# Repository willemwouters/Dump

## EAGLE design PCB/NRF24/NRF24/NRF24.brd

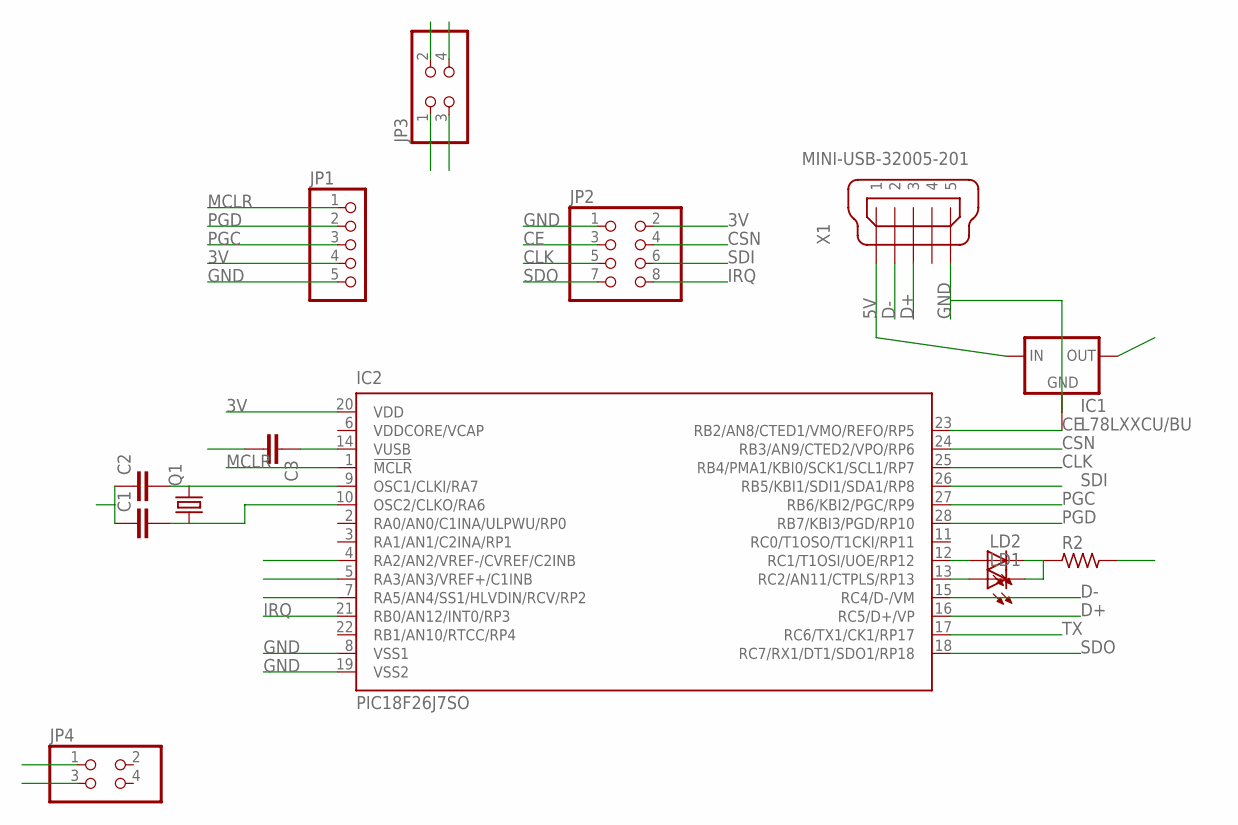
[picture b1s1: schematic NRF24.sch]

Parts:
C1, C2: C-EU025-025X050; C025-025X050
C3: C-EU050-025X075; C050-025X075
IC1: L78LXXCU/BU; SOT89
IC2: PIC18F26J7SO; SO28W
JP1: PINHD-1X5; 1X05
JP2: PINHD-2X4; 2X04
JP3, JP4: PINHD-2X2; 2X02
LD1, LD2: LED5MM
Q1: CRYTALHC49S; HC49/S
R2: R_X0204/5; 0204/5
X1: MINI-USB-32005-201; 32005-201

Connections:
3V: IC1.1 (OUT), IC2.20 (VDD), JP1.4, JP2.2
5V: IC1.3 (IN), X1.1
CE: IC2.23 (RB2/AN8/CTED1/VMO/REFO/RP5), JP2.3
CLK: IC2.25 (RB4/PMA1/KBI0/SCK1/SCL1/RP7), JP2.5
CSN: IC2.24 (RB3/AN9/CTED2/VPO/RP6), JP2.4
D+: IC2.16 (RC5/D+/VP), X1.3
D-: IC2.15 (RC4/D-/VM), X1.2
GND: C1.1, C2.1, C3.2, IC1.2 (GND), IC2.8 (VSS1), IC2.19 (VSS2), JP1.5, JP2.1, R2.2, X1.5
IRQ: IC2.21 (RB0/AN12/INT0/RP3), JP2.8
MCLR: IC2.1 (!MCLR), JP1.1
unnamed: IC2.13 (RC2/AN11/CTPLS/RP13), LD1.A
unnamed: LD1.K (C), LD2.K (C), R2.1
unnamed: IC2.12 (RC1/T1OSI/UOE/RP12), LD2.A
unnamed: C1.2, IC2.10 (OSC2/CLKO/RA6), Q1.1
unnamed: C2.2, IC2.9 (OSC1/CLKI/RA7), Q1.2
unnamed: C3.1, IC2.14 (VUSB)
PGC: IC2.27 (RB6/KBI2/PGC/RP9), JP1.3
PGD: IC2.28 (RB7/KBI3/PGD/RP10), JP1.2
RA2: IC2.4 (RA2/AN2/VREF-/CVREF/C2INB), JP3.1
RA3: IC2.5 (RA3/AN3/VREF+/C1INB), JP3.3
RA5: IC2.7 (RA5/AN4/SS1/HLVDIN/RCV/RP2), JP3.2
SDI: IC2.26 (RB5/KBI1/SDI1/SDA1/RP8), JP2.6
SDO: IC2.18 (RC7/RX1/DT1/SDO1/RP18), JP2.7, JP4.1
TX: IC2.17 (RC6/TX1/CK1/RP17), JP4.3

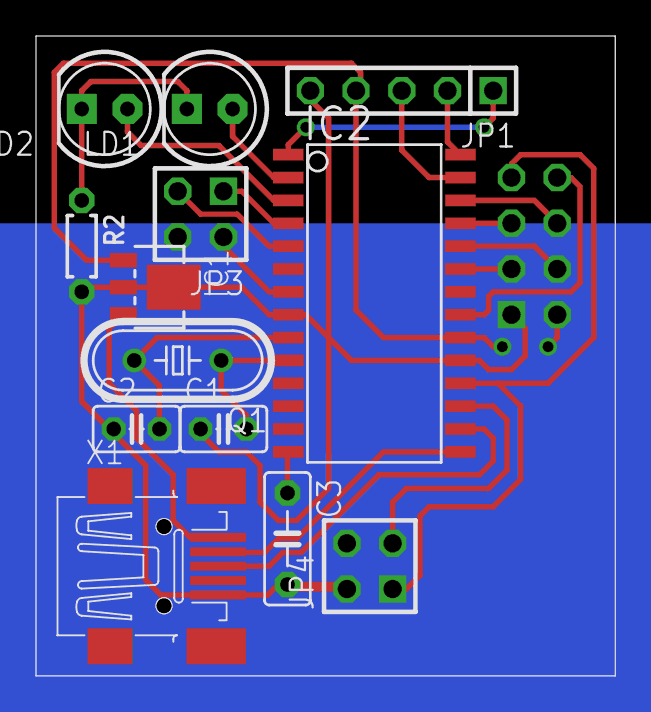
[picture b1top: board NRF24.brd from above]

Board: 2 copper layers, 32.2 x 35.5 mm, 14 parts (1 on the bottom side), 24 nets.

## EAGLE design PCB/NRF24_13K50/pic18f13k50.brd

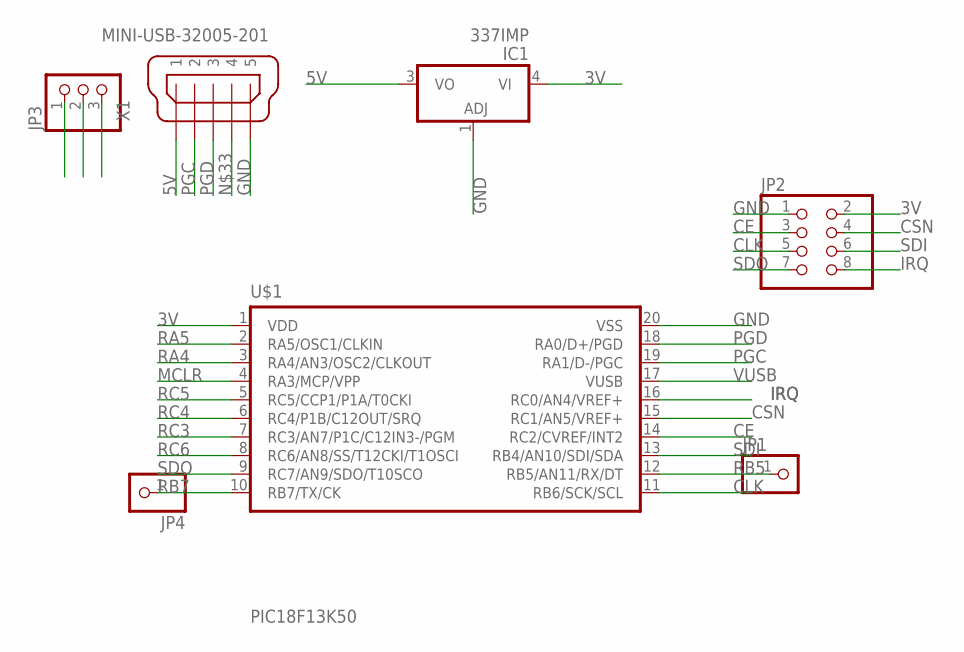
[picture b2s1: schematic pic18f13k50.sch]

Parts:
IC1: 337IMP; SOT223
JP1, JP4: PINHD-1X1; 1X01
JP2: PINHD-2X4; 2X04
JP3: PINHD-1X3; 1X03
U$1: PIC18F13K50; SSOP20
X1: MINI-USB-32005-201; 32005-201

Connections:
3V: IC1.4 (VI), JP2.2, JP3.2, U$1.1 (VDD)
5V: IC1.3 (VO), JP3.3, X1.1
CE: JP2.3, U$1.14 (RC2/CVREF/INT2)
CLK: JP2.5, U$1.11 (RB6/SCK/SCL)
CSN: JP2.4, U$1.15 (RC1/AN5/VREF+)
GND: IC1.1 (ADJ), JP2.1, U$1.20 (VSS), X1.5
IRQ: JP2.8, U$1.16 (RC0/AN4/VREF+)
MCLR: JP3.1, U$1.4 (RA3/MCP/VPP)
PGC: U$1.19 (RA1/D-/PGC), X1.2
PGD: U$1.18 (RA0/D+/PGD), X1.3
RA4: U$1.3 (RA4/AN3/OSC2/CLKOUT)
RA5: U$1.2 (RA5/OSC1/CLKIN)
RB5: JP1.1, U$1.12 (RB5/AN11/RX/DT)
RB7: JP4.1, U$1.10 (RB7/TX/CK)
RC3: U$1.7 (RC3/AN7/P1C/C12IN3-/PGM)
RC4: U$1.6 (RC4/P1B/C12OUT/SRQ)
RC5: U$1.5 (RC5/CCP1/P1A/T0CKI)
RC6: U$1.8 (RC6/AN8/SS/T12CKI/T1OSCI)
SDI: JP2.6, U$1.13 (RB4/AN10/SDI/SDA)
SDO: JP2.7, U$1.9 (RC7/AN9/SDO/T10SCO)
VUSB: U$1.17 (VUSB)

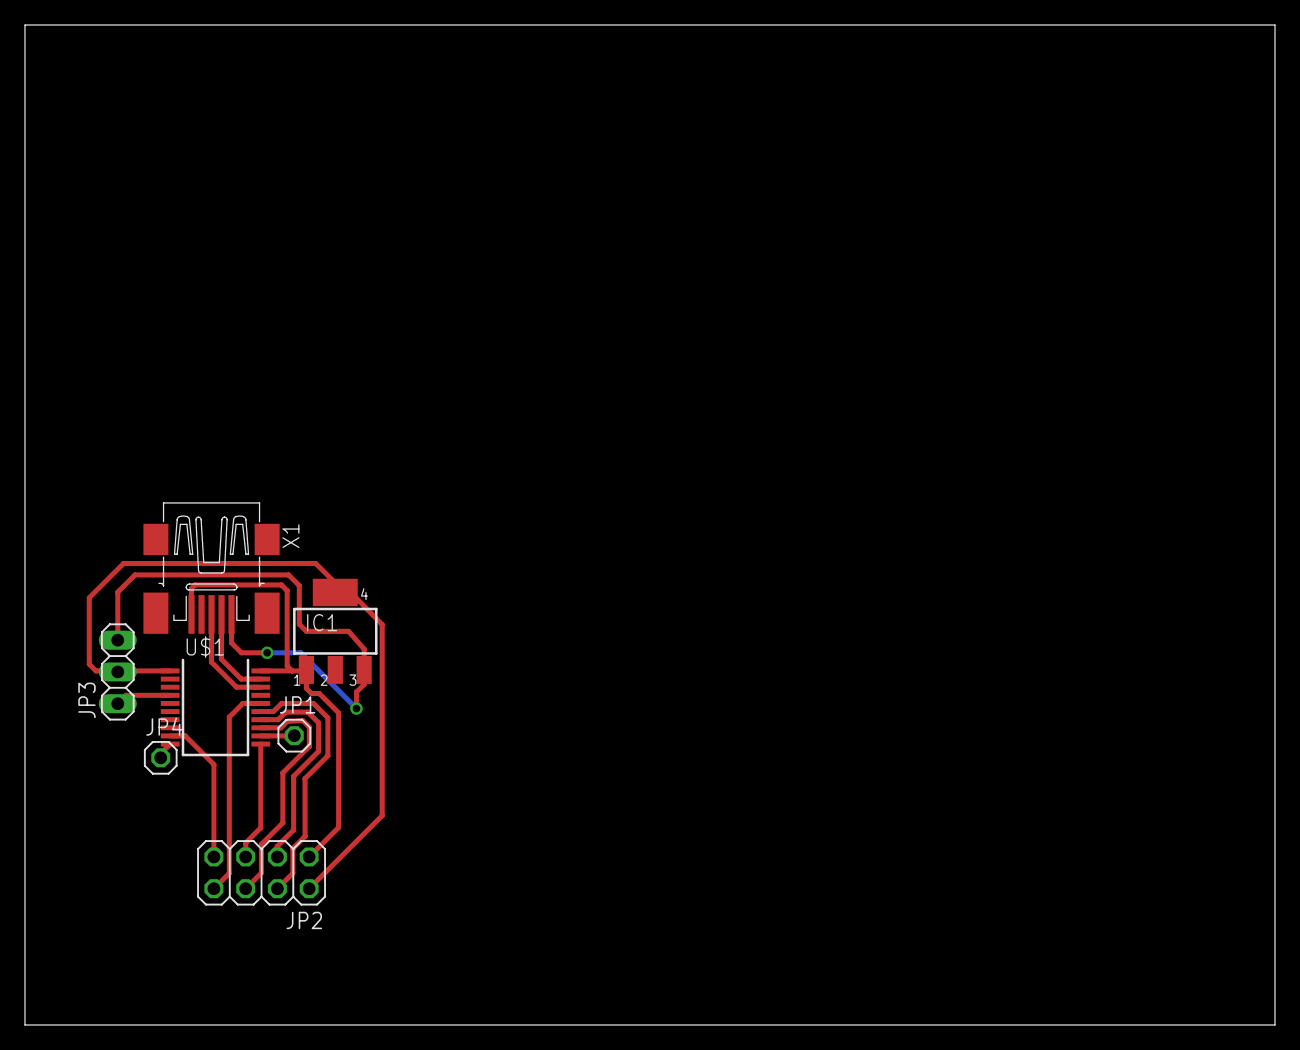
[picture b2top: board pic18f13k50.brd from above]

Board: 2 copper layers, 100.0 x 80.0 mm, 7 parts (0 on the bottom side), 14 nets.

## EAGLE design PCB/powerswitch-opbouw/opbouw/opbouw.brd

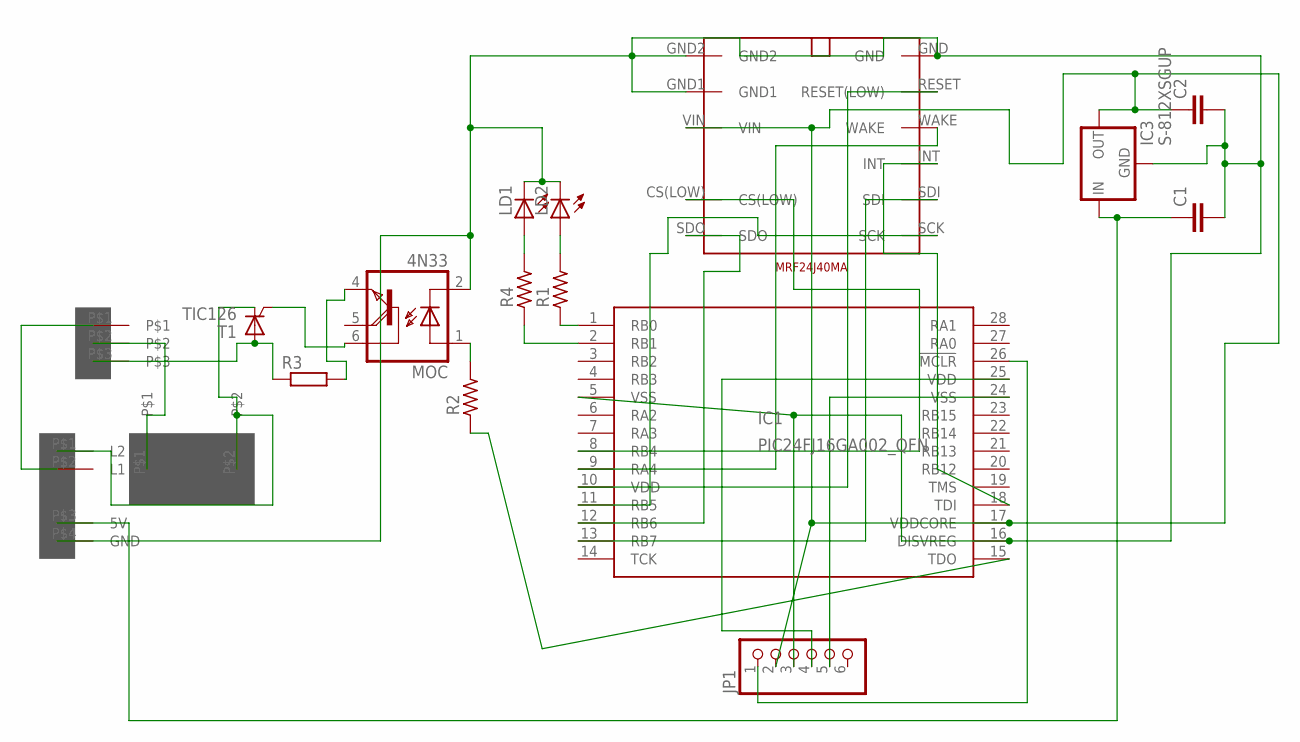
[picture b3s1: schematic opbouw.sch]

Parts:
C1, C2: C-EUC0805K; C0805K
IC1: PIC24FJ16GA002_QFN; QFN28-ML_6X6MM
IC3: S-812XSGUP; SOT89
JP1: PINHD-1X6; 1X06
LD1, LD2: LEDCHIPLED_0805; CHIPLED_0805
MOC: 4N33; DIL06
R1, R2, R4: R_0805; R0805
R3: R-EU_0207/10; 0207/10
T1: TIC126; TO220CS
U$1: MRF24J40MA
U$2: CONNECTOR
U$3: FUSEFUSE; FUSE
U$4: BIAS

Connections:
unnamed: C2.1, IC1.17 (VDDCORE), IC3.3 (OUT), JP1.2, U$1.VIN
unnamed: IC1.26 (!MCLR), JP1.1
unnamed: IC1.25 (VDD), JP1.4
unnamed: IC1.24 (VSS), JP1.5
unnamed: IC1.8 (RB4), U$1.CS(LOW)
unnamed: IC1.15 (TDO), R2.1
unnamed: IC1.10 (VDD), U$1.RESET (RESET(LOW))
unnamed: IC1.13 (RB7), U$1.SDI
unnamed: IC1.18 (TDI), U$1.INT
unnamed: IC1.9 (RA4), U$1.WAKE
unnamed: IC1.11 (RB5), U$1.SCK
unnamed: MOC.6 (B), T1.G
unnamed: MOC.1 (A), R2.2
unnamed: IC1.12 (RB6), U$1.SDO
unnamed: MOC.4 (E), R3.2
unnamed: U$2.P$2, U$3.P$1
unnamed: R3.1, T1.A, U$2.P$3
unnamed: IC1.1 (RB0), R1.1
unnamed: IC1.2 (RB1), R4.1
unnamed: LD2.A, R1.2
unnamed: LD1.A, R4.2
unnamed: C1.2, C2.2, IC1.5 (VSS), IC1.16 (DISVREG), IC3.1 (GND), JP1.3, LD1.C, LD2.C, MOC.2 (C), U$1.GND, U$1.GND1, U$1.GND2, U$4.P$4 (GND)
unnamed: C1.1, IC3.2 (IN), U$4.P$3 (5V)
unnamed: T1.C, U$3.P$2, U$4.P$1 (L2)
unnamed: U$2.P$1, U$4.P$2 (L1)

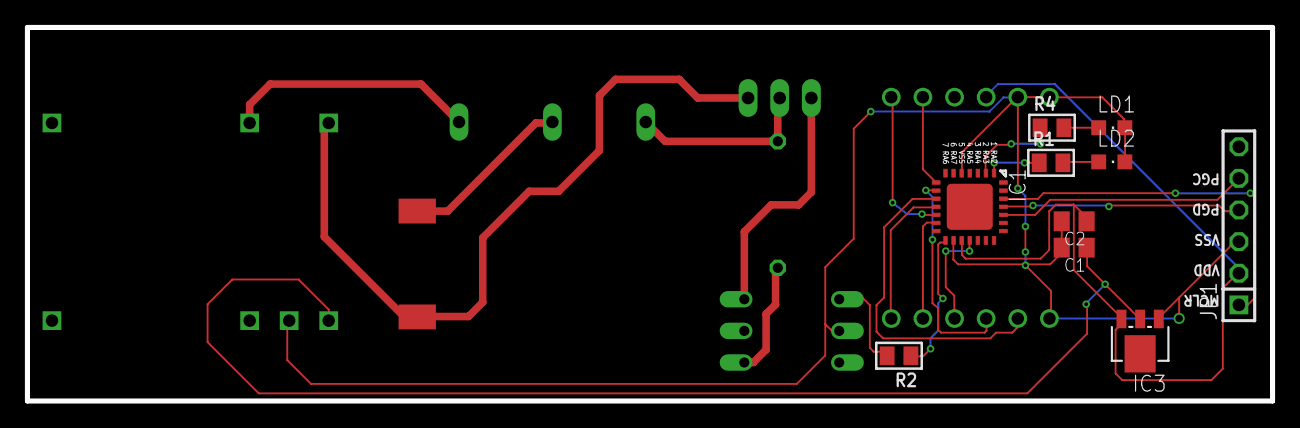
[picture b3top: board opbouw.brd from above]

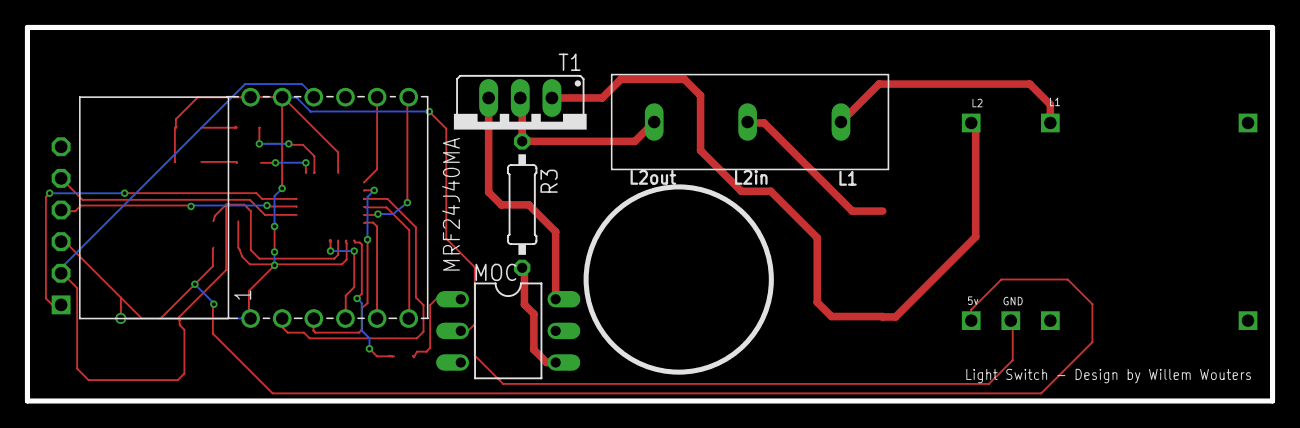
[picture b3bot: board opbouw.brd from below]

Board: 2 copper layers, 100.0 x 30.0 mm, 17 parts (5 on the bottom side), 25 nets.

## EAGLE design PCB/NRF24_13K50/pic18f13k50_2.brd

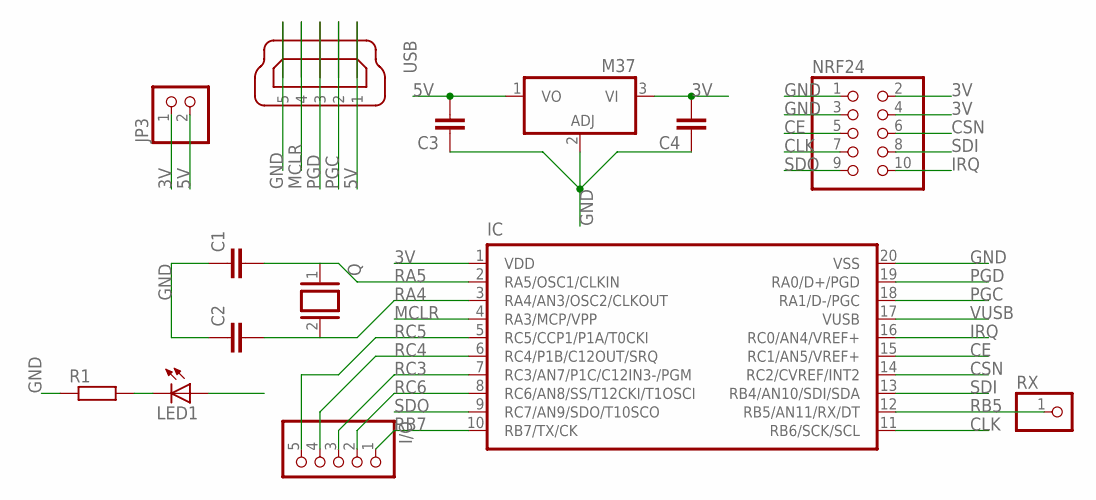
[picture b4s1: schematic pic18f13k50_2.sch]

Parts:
C1, C2: C-EUC0805; C0805
C3, C4: C-EU025-025X050; C025-025X050
I/O: PINHD-1X5; 1X05
IC: PIC18F13K50; SSOP20
JP3: PINHD-1X2; 1X02
LED1: LEDCHIP-LED0805; CHIP-LED0805
M37: 337IMP; SOT223
NRF24: PINHD-2X5; 2X05
Q: XTAL/S; QS
R1: R; R0805
RX: PINHD-1X1; 1X01
USB: MINI-USB-32005-201; 32005-201

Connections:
3V: C4.2, IC.1 (VDD), JP3.1, M37.3 (VI), NRF24.2, NRF24.4
5V: C3.2, JP3.2, M37.1 (VO), USB.1
CE: IC.15 (RC1/AN5/VREF+), NRF24.5
CLK: IC.11 (RB6/SCK/SCL), NRF24.7
CSN: IC.14 (RC2/CVREF/INT2), NRF24.6
GND: C1.1, C2.1, C3.1, C4.1, IC.20 (VSS), M37.2 (ADJ), NRF24.1, NRF24.3, R1.1, USB.5
IRQ: IC.16 (RC0/AN4/VREF+), NRF24.10
MCLR: IC.4 (RA3/MCP/VPP), USB.4
unnamed: LED1.C, R1.2
PGC: IC.18 (RA1/D-/PGC), USB.2
PGD: IC.19 (RA0/D+/PGD), USB.3
RA4: C2.2, IC.3 (RA4/AN3/OSC2/CLKOUT), Q.2
RA5: C1.2, IC.2 (RA5/OSC1/CLKIN), Q.1
RB5: IC.12 (RB5/AN11/RX/DT), RX.1
RB7: I/O.1, IC.10 (RB7/TX/CK), LED1.A
RC3: I/O.3, IC.7 (RC3/AN7/P1C/C12IN3-/PGM)
RC4: I/O.4, IC.6 (RC4/P1B/C12OUT/SRQ)
RC5: I/O.5, IC.5 (RC5/CCP1/P1A/T0CKI)
RC6: I/O.2, IC.8 (RC6/AN8/SS/T12CKI/T1OSCI)
SDI: IC.13 (RB4/AN10/SDI/SDA), NRF24.8
SDO: IC.9 (RC7/AN9/SDO/T10SCO), NRF24.9
VUSB: IC.17 (VUSB)

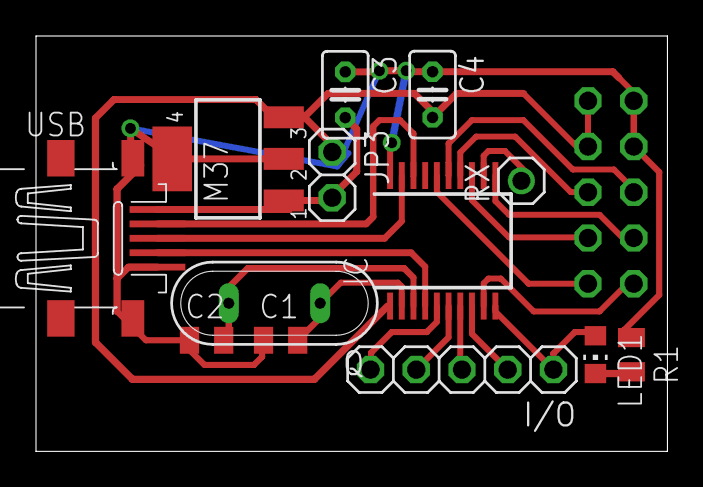
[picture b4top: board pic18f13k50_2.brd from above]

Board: 2 copper layers, 35.1 x 23.1 mm, 14 parts (1 on the bottom side), 21 nets.

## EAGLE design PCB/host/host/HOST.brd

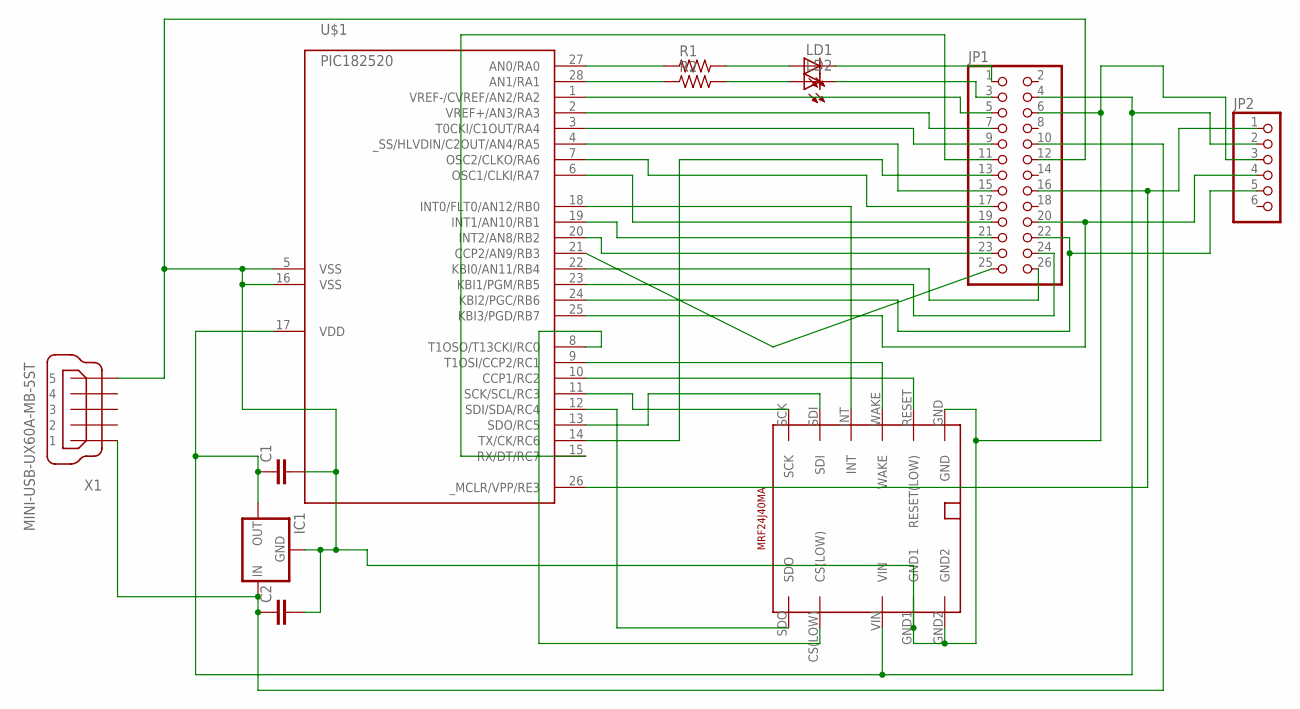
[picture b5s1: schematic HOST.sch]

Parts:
C1, C2: C-EUC0805; C0805
IC1: 78LXX-SOT89; SOT89
JP1: PINHD-2X13_2.54; 2X13
JP2: PINHD-1X6; 1X06
LD1, LD2: LEDCHIPLED_0805; CHIPLED_0805
R1, R2: R_0805; R0805
U$1: PIC182520; QFN28
U$2: MRF24J40MA
X1: MINI-USB-UX60A-MB-5ST; UX60A-MB-5ST

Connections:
unnamed: U$1.12 (SDI/SDA/RC4), U$2.SDO
unnamed: U$1.8 (T1OSO/T13CKI/RC0), U$2.CS(LOW)
unnamed: U$1.10 (CCP1/RC2), U$2.RESET (RESET(LOW))
unnamed: U$1.11 (SCK/SCL/RC3), U$2.SCK
unnamed: U$1.13 (SDO/RC5), U$2.SDI
unnamed: U$1.18 (INT0/FLT0/AN12/RB0), U$2.INT
unnamed: U$1.9 (T1OSI/CCP2/RC1), U$2.WAKE
unnamed: JP1.13, U$1.14 (TX/CK/RC6)
unnamed: C1.2, C2.2, IC1.1 (GND), JP1.6, JP1.12, JP2.3, U$1.5 (VSS), U$1.16 (VSS), U$2.GND, U$2.GND1, U$2.GND2, X1.5
unnamed: JP1.11, U$1.15 (RX/DT/RC7)
unnamed: C2.1, IC1.2 (IN), JP1.10, X1.1
unnamed: R1.1, U$1.27 (AN0/RA0)
unnamed: R2.1, U$1.28 (AN1/RA1)
unnamed: LD2.A, R2.2
unnamed: LD1.A, R1.2
unnamed: JP1.1, LD1.C
unnamed: JP1.3, LD2.C
unnamed: JP1.5, U$1.1 (VREF-/CVREF/AN2/RA2)
unnamed: JP1.7, U$1.2 (VREF+/AN3/RA3)
unnamed: JP1.9, U$1.3 (T0CKI/C1OUT/RA4)
unnamed: JP1.21, U$1.19 (INT1/AN10/RB1)
unnamed: JP1.19, U$1.6 (OSC1/CLKI/RA7)
unnamed: JP1.15, U$1.4 (_SS/HLVDIN/C2OUT/AN4/RA5)
unnamed: JP1.17, U$1.7 (OSC2/CLKO/RA6)
unnamed: JP1.23, U$1.20 (INT2/AN8/RB2)
unnamed: JP1.25, U$1.21 (CCP2/AN9/RB3)
unnamed: JP1.26, U$1.22 (KBI0/AN11/RB4)
unnamed: JP1.24, U$1.23 (KBI1/PGM/RB5)
unnamed: JP1.22, JP2.5, U$1.24 (KBI2/PGC/RB6)
unnamed: JP1.20, JP2.4, U$1.25 (KBI3/PGD/RB7)
unnamed: JP1.16, JP2.1, U$1.26 (_MCLR/VPP/RE3)
unnamed: C1.1, IC1.3 (OUT), JP1.4, JP2.2, U$1.17 (VDD), U$2.VIN

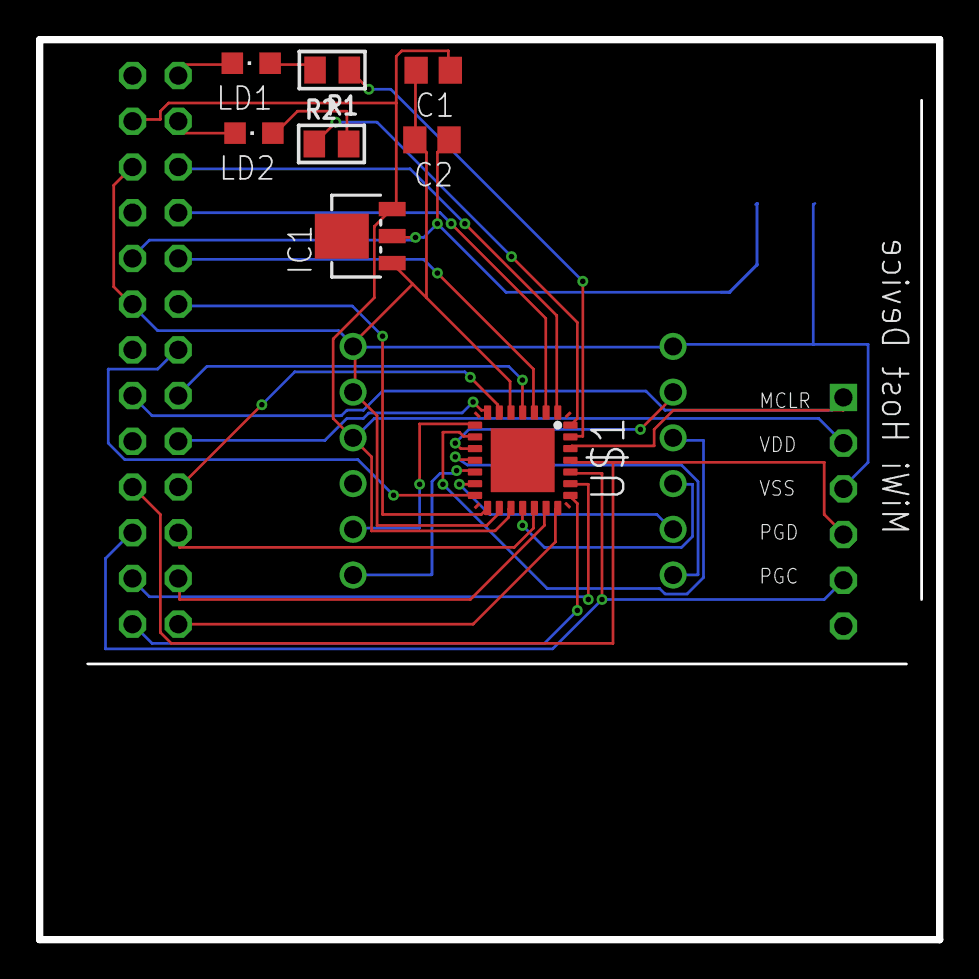
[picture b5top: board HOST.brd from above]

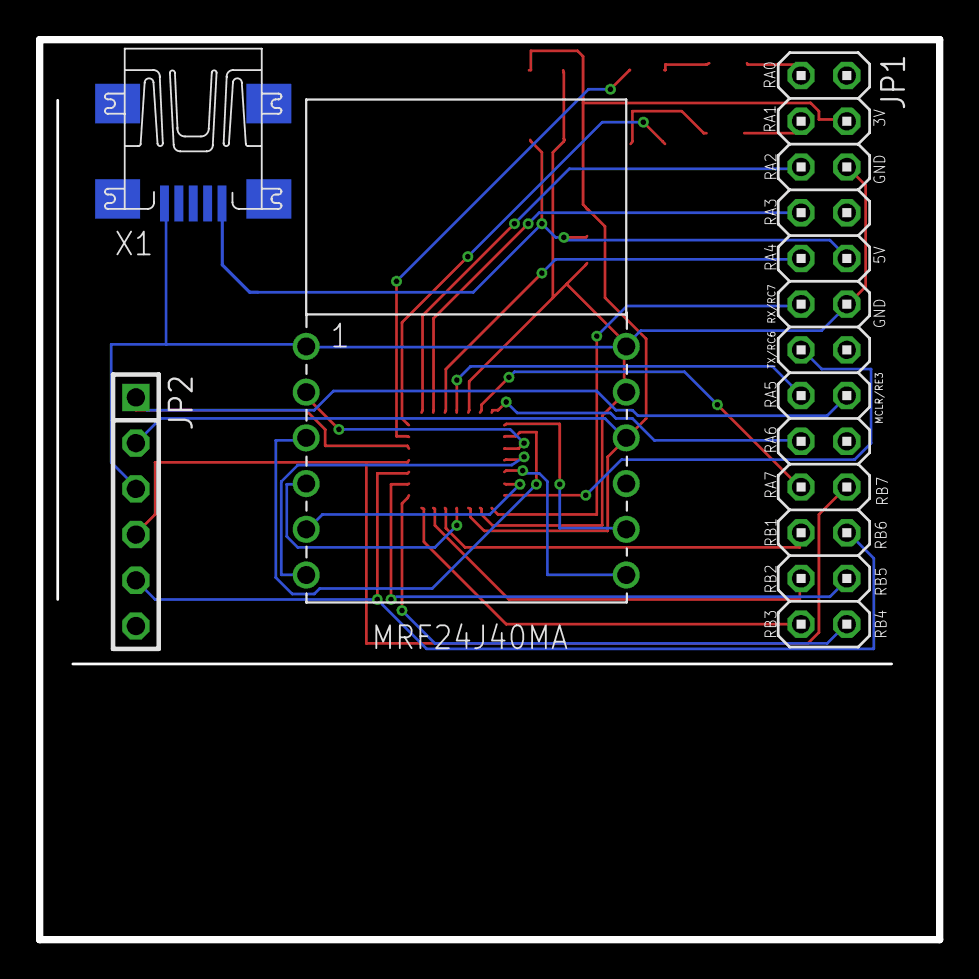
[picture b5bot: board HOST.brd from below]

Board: 2 copper layers, 50.0 x 50.0 mm, 12 parts (4 on the bottom side), 32 nets.

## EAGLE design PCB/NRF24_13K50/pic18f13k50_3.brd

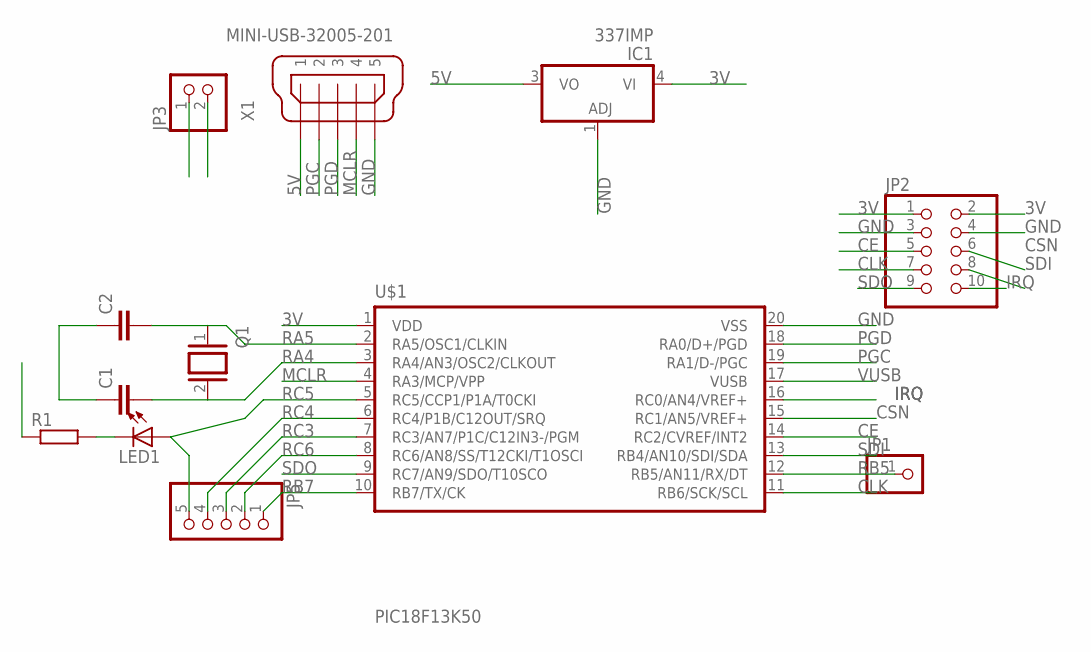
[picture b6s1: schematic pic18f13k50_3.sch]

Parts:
C1, C2: C-EUC0805; C0805
IC1: 337IMP; SOT223
JP1: PINHD-1X1; 1X01
JP2: PINHD-2X5; 2X05
JP3: PINHD-1X2; 1X02
JP5: PINHD-1X5; 1X05
LED1: LEDCHIP-LED0805; CHIP-LED0805
Q1: XTAL/S; QS
R1: R; R0805
U$1: PIC18F13K50; SSOP20
X1: MINI-USB-32005-201; 32005-201

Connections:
3V: IC1.4 (VI), JP2.1, JP2.2, JP3.1, R1.1, U$1.1 (VDD)
5V: IC1.3 (VO), JP3.2, X1.1
CE: JP2.5, U$1.14 (RC2/CVREF/INT2)
CLK: JP2.7, U$1.11 (RB6/SCK/SCL)
CSN: JP2.6, U$1.15 (RC1/AN5/VREF+)
GND: C1.1, C2.1, IC1.1 (ADJ), JP2.3, JP2.4, U$1.20 (VSS), X1.5
IRQ: JP2.10, U$1.16 (RC0/AN4/VREF+)
MCLR: U$1.4 (RA3/MCP/VPP), X1.4
unnamed: LED1.C, R1.2
PGC: U$1.19 (RA1/D-/PGC), X1.2
PGD: U$1.18 (RA0/D+/PGD), X1.3
RA4: C1.2, Q1.2, U$1.3 (RA4/AN3/OSC2/CLKOUT)
RA5: C2.2, Q1.1, U$1.2 (RA5/OSC1/CLKIN)
RB5: JP1.1, U$1.12 (RB5/AN11/RX/DT)
RB7: JP5.1, U$1.10 (RB7/TX/CK)
RC3: JP5.3, U$1.7 (RC3/AN7/P1C/C12IN3-/PGM)
RC4: JP5.4, U$1.6 (RC4/P1B/C12OUT/SRQ)
RC5: JP5.5, LED1.A, U$1.5 (RC5/CCP1/P1A/T0CKI)
RC6: JP5.2, U$1.8 (RC6/AN8/SS/T12CKI/T1OSCI)
SDI: JP2.8, U$1.13 (RB4/AN10/SDI/SDA)
SDO: JP2.9, U$1.9 (RC7/AN9/SDO/T10SCO)
VUSB: U$1.17 (VUSB)

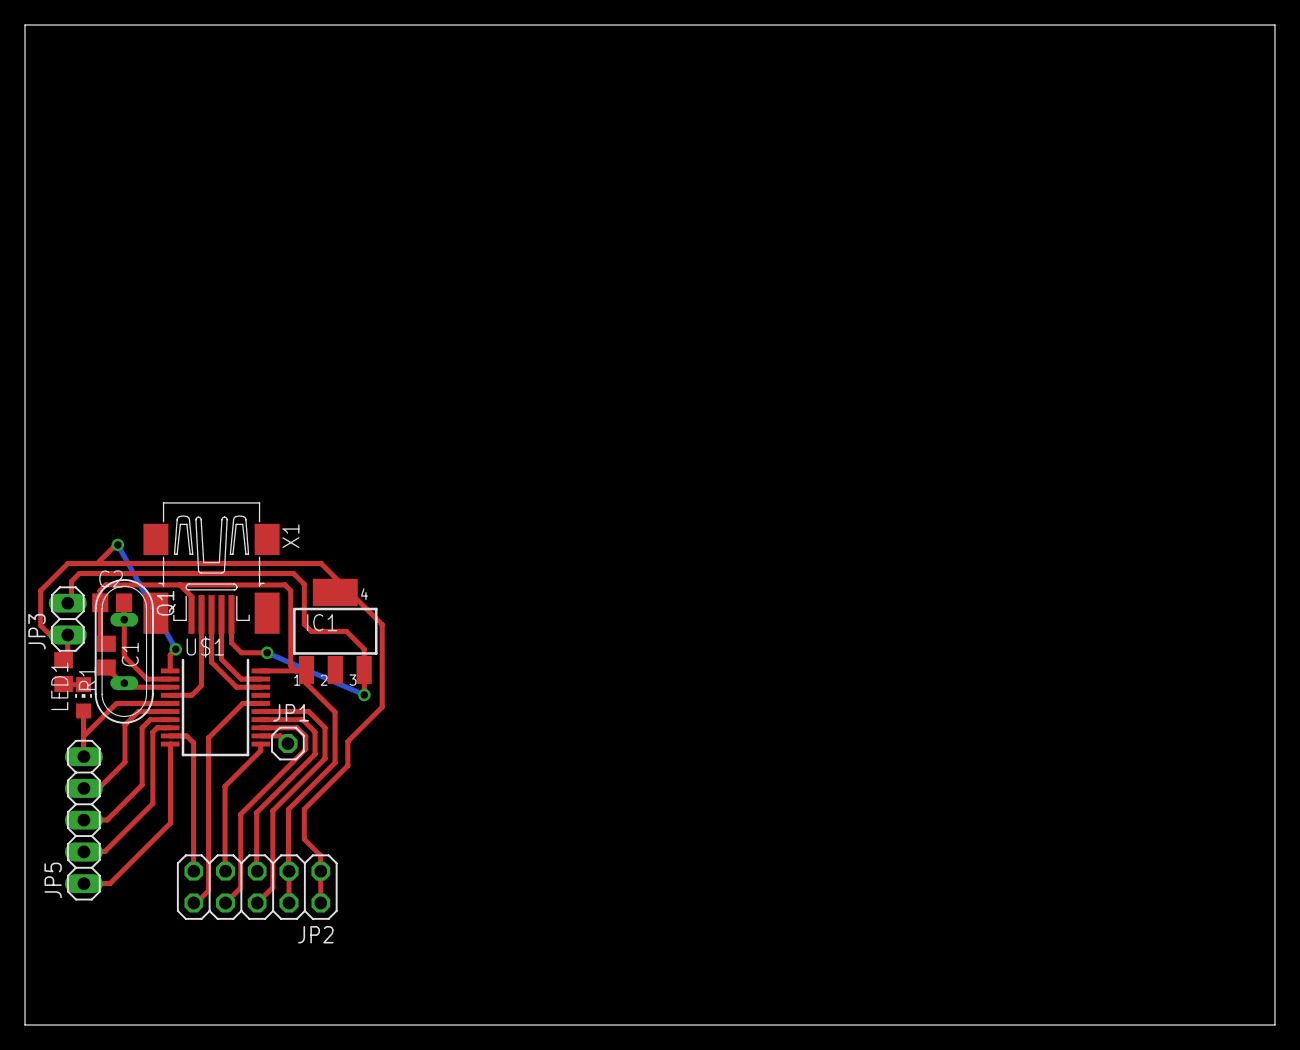
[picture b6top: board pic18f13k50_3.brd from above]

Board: 2 copper layers, 100.0 x 80.0 mm, 12 parts (0 on the bottom side), 21 nets.

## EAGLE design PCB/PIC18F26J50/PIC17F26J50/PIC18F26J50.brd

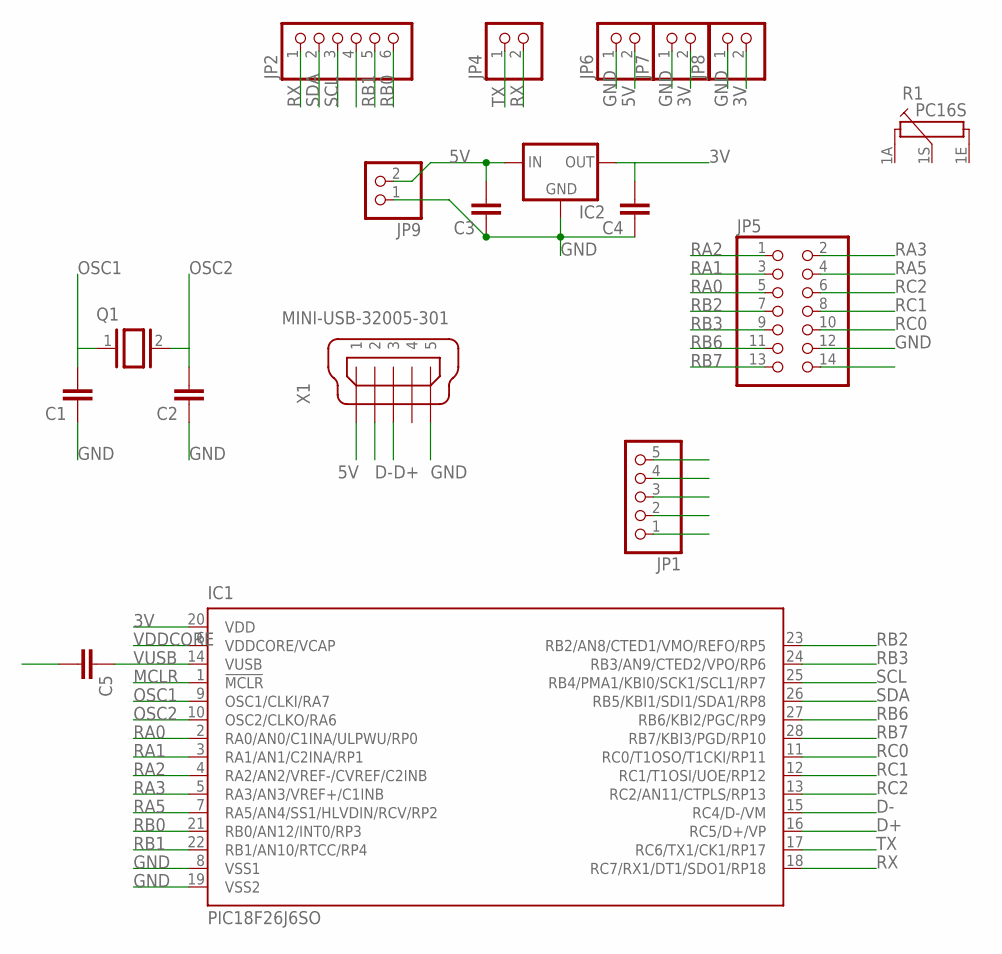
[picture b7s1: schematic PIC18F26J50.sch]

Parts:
C1, C2, C3, C4, C5: C-EU025-025X050; C025-025X050
IC1: PIC18F26J6SO; SO28W
IC2: 78LXX-SOT89; SOT89
JP1: PINHD-1X5; 1X05
JP2: PINHD-1X6; 1X06
JP4, JP6, JP7, JP8, JP9: PINHD-1X2; 1X02
JP5: PINHD-2X7; 2X07
Q1: XTAL/S; QS
R1: PC16S
X1: MINI-USB-32005-301; 32005-301

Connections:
3V: C4.2, IC1.20 (VDD), IC2.1 (OUT), JP1.4, JP7.2, JP8.2
5V: C3.2, IC2.3 (IN), JP6.2, JP9.2, X1.1
D+: IC1.16 (RC5/D+/VP), X1.3
D-: IC1.15 (RC4/D-/VM), X1.2
GND: C1.1, C2.1, C3.1, C4.1, C5.2, IC1.8 (VSS1), IC1.19 (VSS2), IC2.2 (GND), JP1.5, JP5.12, JP5.14, JP6.1, JP7.1, JP8.1, JP9.1, X1.5
MCLR: IC1.1 (!MCLR), JP1.1
OSC1: C1.2, IC1.9 (OSC1/CLKI/RA7), Q1.1
OSC2: C2.2, IC1.10 (OSC2/CLKO/RA6), Q1.2
RA0: IC1.2 (RA0/AN0/C1INA/ULPWU/RP0), JP5.5
RA1: IC1.3 (RA1/AN1/C2INA/RP1), JP5.3
RA2: IC1.4 (RA2/AN2/VREF-/CVREF/C2INB), JP5.1
RA3: IC1.5 (RA3/AN3/VREF+/C1INB), JP5.2
RA5: IC1.7 (RA5/AN4/SS1/HLVDIN/RCV/RP2), JP5.4
RB0: IC1.21 (RB0/AN12/INT0/RP3), JP2.6
RB1: IC1.22 (RB1/AN10/RTCC/RP4), JP2.5
RB2: IC1.23 (RB2/AN8/CTED1/VMO/REFO/RP5), JP2.4, JP5.7
RB3: IC1.24 (RB3/AN9/CTED2/VPO/RP6), JP5.9
RB6: IC1.27 (RB6/KBI2/PGC/RP9), JP1.2, JP5.11
RB7: IC1.28 (RB7/KBI3/PGD/RP10), JP1.3, JP5.13
RC0: IC1.11 (RC0/T1OSO/T1CKI/RP11), JP5.10
RC1: IC1.12 (RC1/T1OSI/UOE/RP12), JP5.8
RC2: IC1.13 (RC2/AN11/CTPLS/RP13), JP5.6
RX: IC1.18 (RC7/RX1/DT1/SDO1/RP18), JP2.1, JP4.2
SCL: IC1.25 (RB4/PMA1/KBI0/SCK1/SCL1/RP7), JP2.3
SDA: IC1.26 (RB5/KBI1/SDI1/SDA1/RP8), JP2.2
TX: IC1.17 (RC6/TX1/CK1/RP17), JP4.1
VDDCORE: IC1.6 (VDDCORE/VCAP)
VUSB: C5.1, IC1.14 (VUSB)

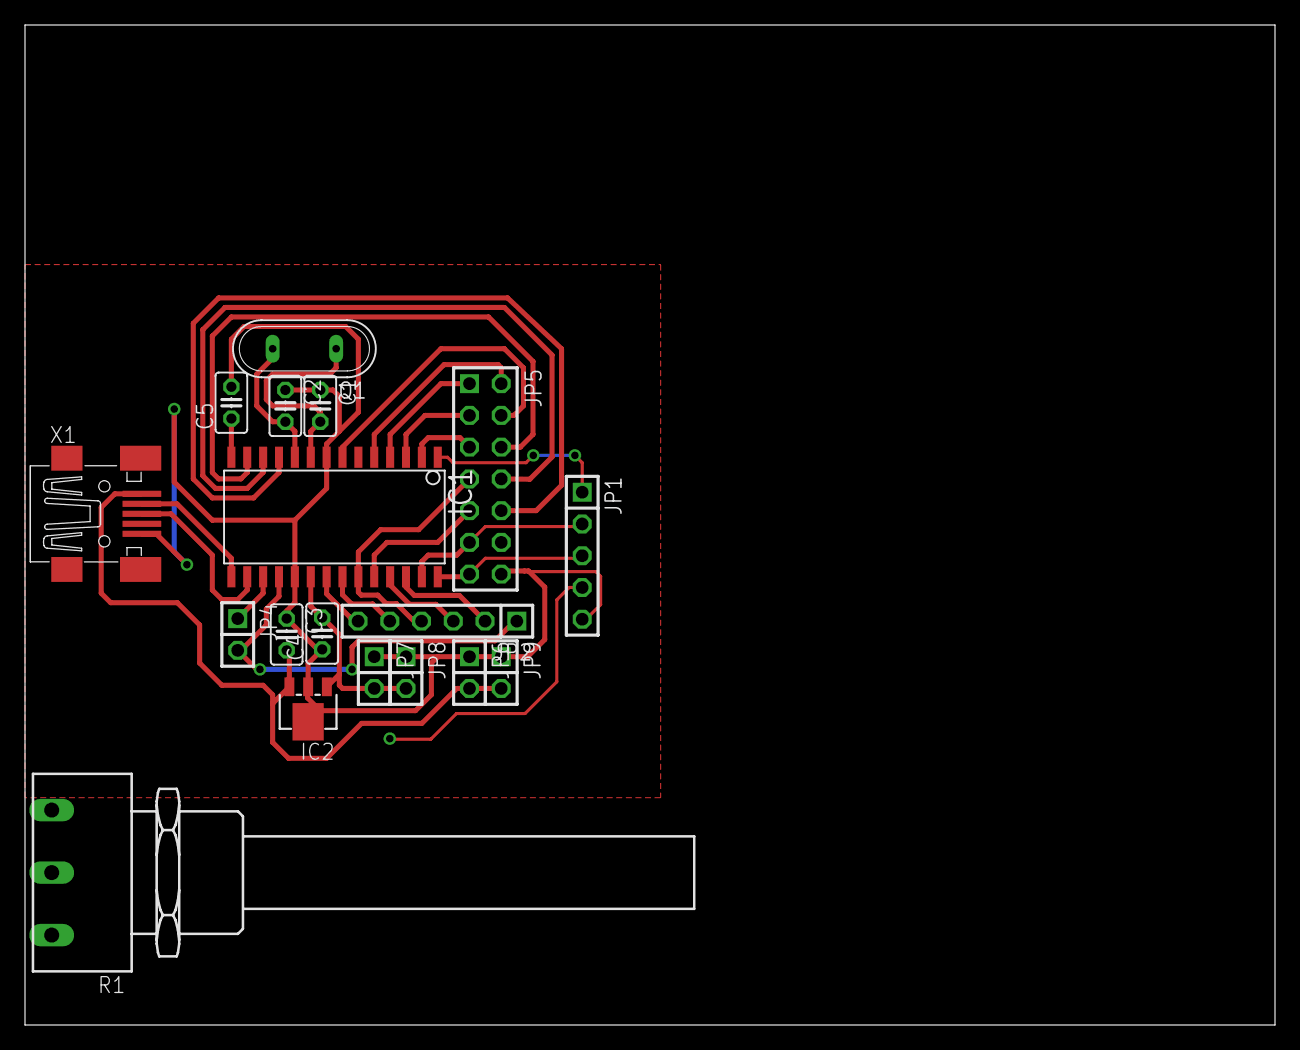
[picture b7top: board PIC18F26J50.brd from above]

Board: 2 copper layers, 100.0 x 80.0 mm, 18 parts (0 on the bottom side), 27 nets.

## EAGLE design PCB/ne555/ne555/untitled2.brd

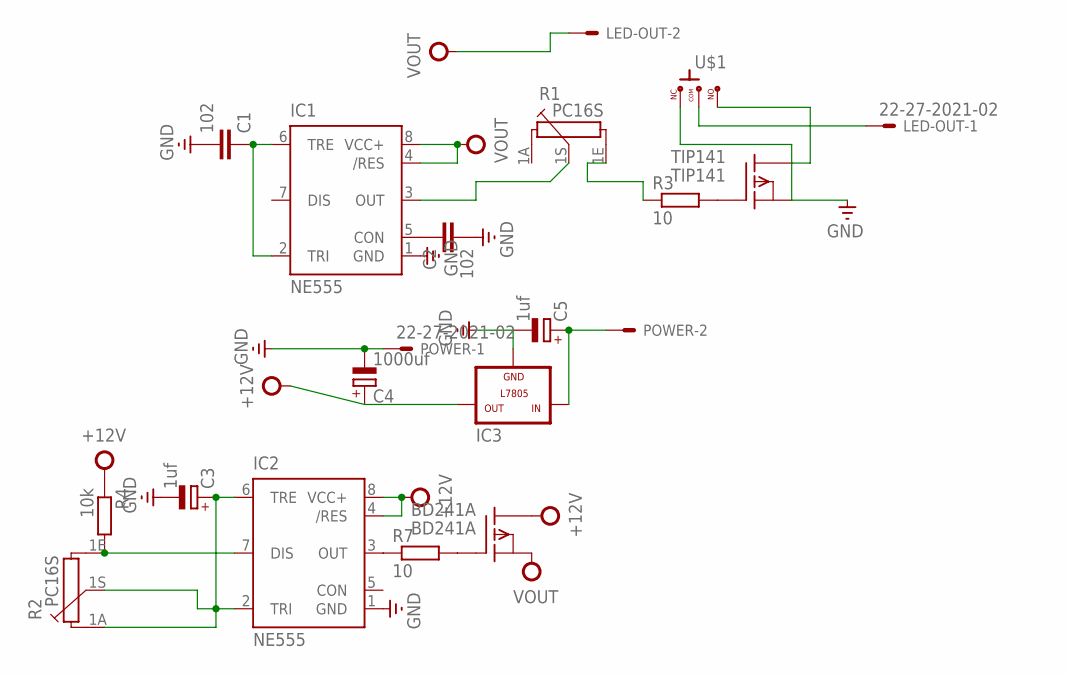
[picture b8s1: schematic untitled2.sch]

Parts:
BD241A: BD241A; TO220
C1, C2: 102; C050-024X044
C3, C5: 1uf; E5-4
C4: 1000uf; E5-4
IC1, IC2: NE555; DIL-08
IC3: L7805; 78XXL
LED-OUT: 22-27-2021-02; 6410-02
POWER: 22-27-2021-02; 6410-02
R1, R2: PC16S
R3, R7: 10; 0207/7
R4: 10k; 0207/7
TIP141: TIP141; TO220
U$1: -SLIDERS; CON3

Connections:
+12V: BD241A.2 (D), C4.+, IC2.4 (/RES), IC2.8 (VCC+), IC3.OUT, R4.1
GND: C1.2, C2.2, C3.-, C4.-, C5.-, IC1.1 (GND), IC2.1 (GND), IC3.GND, POWER.1, TIP141.3 (S), U$1.P$1 (1)
unnamed: IC1.3 (OUT), R1.1S
unnamed: LED-OUT.1, U$1.P$2 (2)
unnamed: R1.1E, R3.1
unnamed: C2.1, IC1.5 (CON)
unnamed: BD241A.1 (G), R7.2
unnamed: IC2.3 (OUT), R7.1
unnamed: R3.2, TIP141.1 (G)
unnamed: C1.1, IC1.2 (TRI), IC1.6 (TRE)
unnamed: C5.+, IC3.IN, POWER.2
unnamed: TIP141.2 (D), U$1.P$3 (3)
unnamed: C3.+, IC2.2 (TRI), IC2.6 (TRE), R2.1A, R2.1S
unnamed: IC2.7 (DIS), R2.1E, R4.2
VOUT: BD241A.3 (S), IC1.4 (/RES), IC1.8 (VCC+), LED-OUT.2

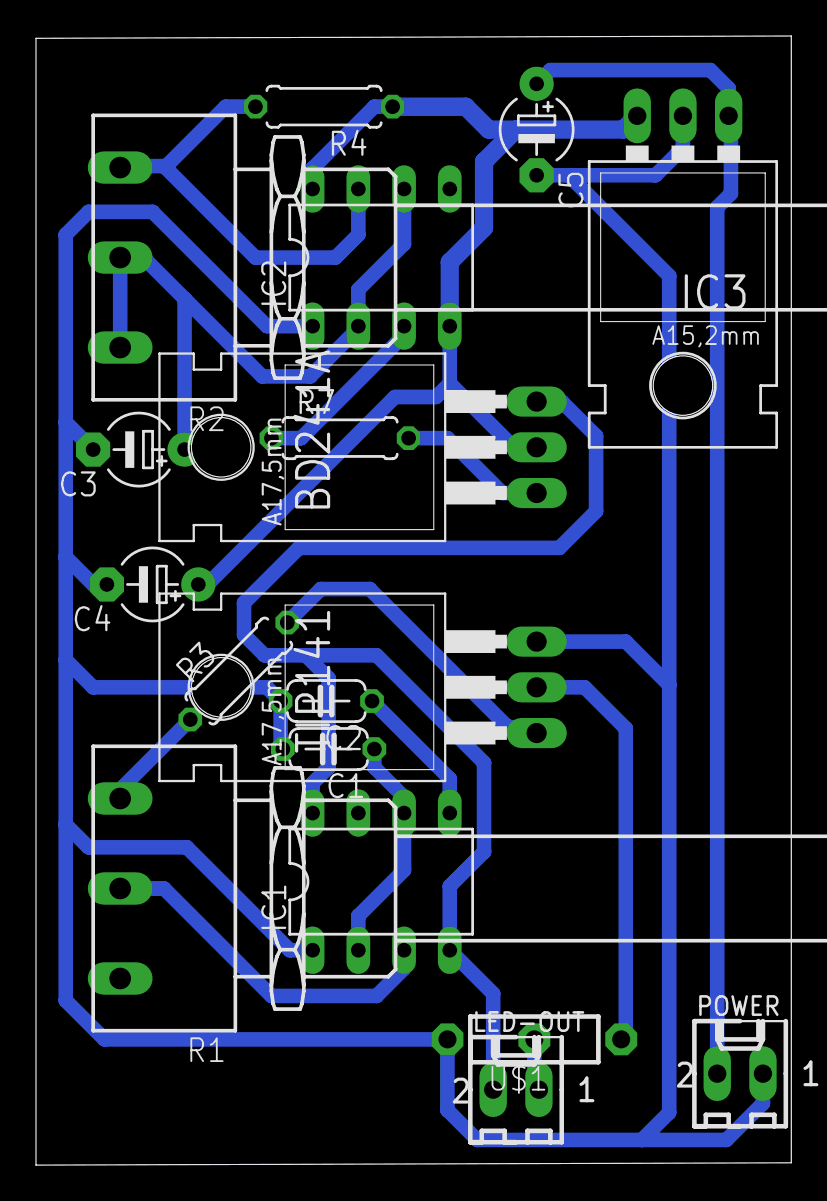
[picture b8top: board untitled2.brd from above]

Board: 2 copper layers, 42.0 x 62.7 mm, 18 parts (0 on the bottom side), 15 nets.

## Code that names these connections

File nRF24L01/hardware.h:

#if defined (HARDWARE_GEN)
	#define SPI_SCK		LATCbits.LATC3		// Clock pin, PORTC pin 3 
	#define SPI_SO		LATCbits.LATC5		// Serial output pin, PORTC pin 5 
	#define SPI_SI		PORTCbits.RC4		// Serial input pin, PORTC pin 4 
	#define SPI_CSN		LATCbits.LATC2		// CSN output pin, PORTC pin 2
	#define SPI_CE		LATCbits.LATC1		// CE output pin, PORTC pin 1
	#define SPI_IRQ		PORTBbits.RB0		// IRQ input pin, PORTB pin 0
	#define SPI_SCALE	4              		// postscaling of signal 
#elif defined (HARDWARE_PROTON) // ** PIC 18F4550
	#define SPI_SCK		LATBbits.LATB1		// Clock pin
	#define SPI_SO		LATCbits.LATC7		// Serial output pin
	#define SPI_SI		PORTBbits.RB0		// Serial input pin
	#define SPI_CSN		LATCbits.LATC1		// CSN output pin
	#define SPI_CE		LATCbits.LATC2		// CE output pin
	#define SPI_IRQ		PORTCbits.RC6		// IRQ input pin

	#define SPI_SCALE	4              		// postscaling of signal 

	#define SPI_SCK_TRIS	TRISBbits.RB1	// IO direção
	#define SPI_SO_TRIS		TRISCbits.RC7	// IO direção
	#define SPI_SI_TRIS		TRISBbits.RB0	// IO direção
	#define SPI_CSN_TRIS	TRISCbits.RC1	// IO direção
	#define SPI_CE_TRIS		TRISCbits.RC2	// IO direção
	#define SPI_IRQ_TRIS	TRISCbits.RC6	// IO direção

#elif defined (HARDWARE_PIC_EXPERT2) // ** PIC 18F4550
	#define SPI_SCK		LATBbits.LATB1		// Clock pin
	#define SPI_SO		LATCbits.LATC7		// Serial output pin
	#define SPI_SI		PORTBbits.RB0		// Serial input pin
	#define SPI_CSN		LATCbits.LATC1		// CSN output pin
	#define SPI_CE		LATCbits.LATC2		// CE output pin
	#define SPI_IRQ		PORTCbits.RC6		// IRQ input pin

	#define SPI_SCALE	4              		// postscaling of signal 

	#define SPI_SCK_TRIS	TRISBbits.RB1	// IO direção
	#define SPI_SO_TRIS		TRISCbits.RC7	// IO direção
	#define SPI_SI_TRIS		TRISBbits.RB0	// IO direção
	#define SPI_CSN_TRIS	TRISCbits.RC1	// IO direção
	#define SPI_CE_TRIS		TRISCbits.RC2	// IO direção
	#define SPI_IRQ_TRIS	TRISCbits.RC6	// IO direção

#else
	#error "Defina Placa Hardware"
#endif

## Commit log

2014-11-19 merging stuff

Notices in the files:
parts and their libraries:
rc-master: Copyright (C) 2007, Bob Starr
